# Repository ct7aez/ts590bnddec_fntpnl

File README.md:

# ts590bnddec_fntpnl
LCD display and buttons for the TS-590 band Decoder.
This is the pcb and sch design for the front panel of the TS-590S(G) Arduino based Band Decoder.
Made by João Cunha Lopes, CT2HME and Pedro Correia, CT7AEZ.
This pcb allows direct connection with the TS-590S(G) Arduino based Band Decoder and provides easy access to the menu buttons and LCD.

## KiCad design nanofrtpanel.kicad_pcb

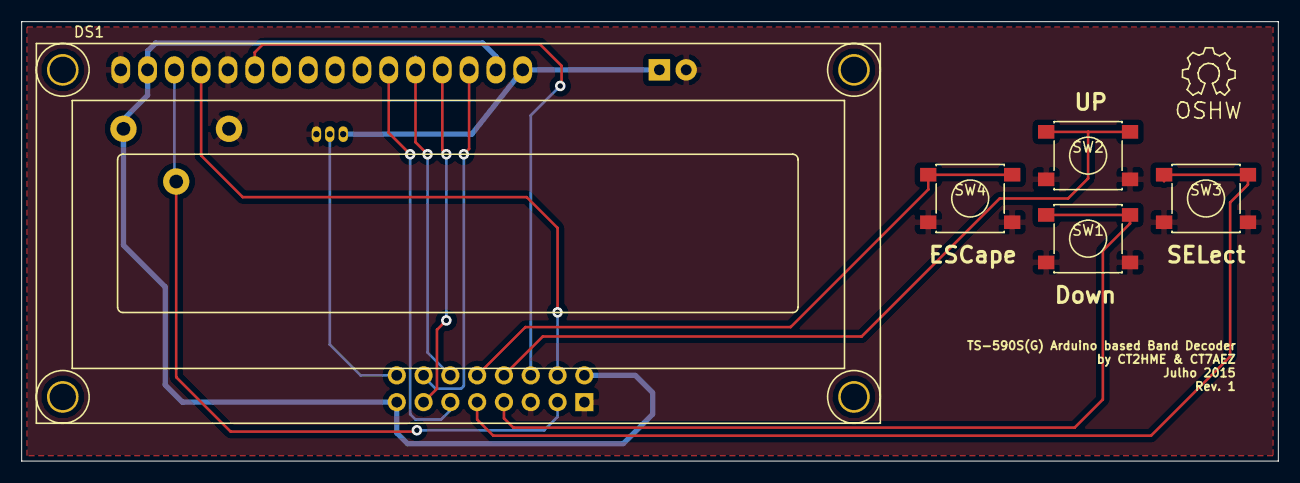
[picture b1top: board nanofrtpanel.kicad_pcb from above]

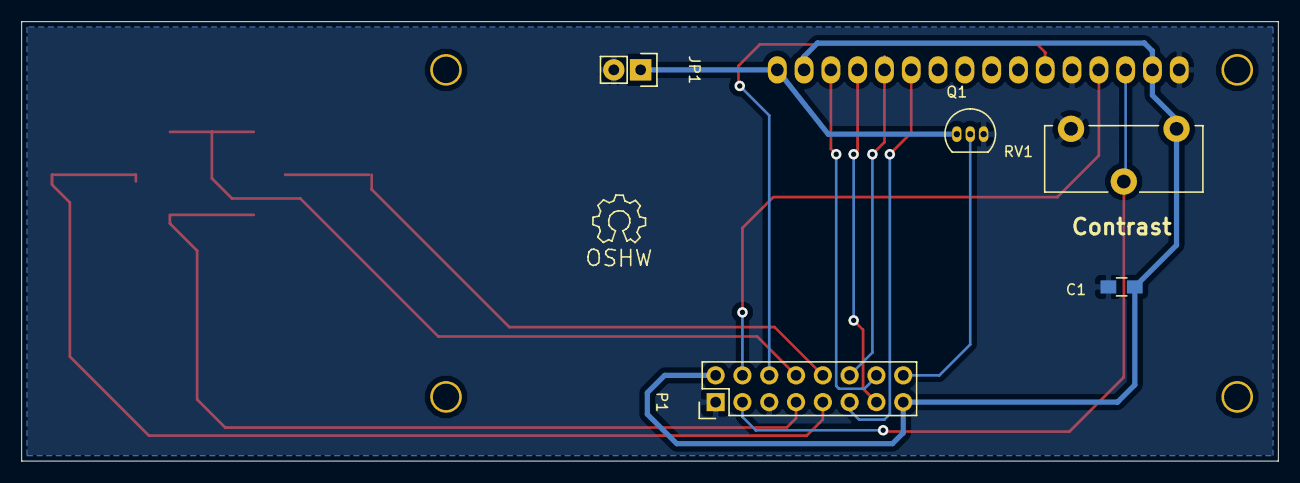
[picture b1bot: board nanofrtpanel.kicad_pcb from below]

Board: 2 copper layers, 119.1 x 41.7 mm, 10 parts (5 on the bottom side), 15 nets.

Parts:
C1: 100n; C_0805_HandSoldering
DS1: LCD-016N002L; WC1602A
JP1: Jumper_NO_Small; Pin_Header_Straight_1x02
P1: CONN_02X08; Pin_Header_Straight_2x08
Q1: BS170; TO-92_Inline_Narrow_Oval
RV1: 10K; Potentiometer_Trimmer-Piher-PT15-h5_vertical
SW1: DOWN; SW_SPST_PTS645
SW2: UP; SW_SPST_PTS645
SW3: SELECT; SW_SPST_PTS645
SW4: ESC; SW_SPST_PTS645

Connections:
+5V: C1.1, DS1.2, DS1.15, P1.2, P1.15, RV1.1
/BCKL: P1.16, Q1.2
/D2: DS1.14, P1.14
/D3: DS1.13, P1.13
/D4: DS1.12, P1.12
/D5: DS1.11, P1.11
/D11: DS1.6, P1.6
/D12: DS1.4, P1.4
/SW1: P1.7, SW1.1
/SW2: P1.8, SW2.1
/SW3: P1.9, SW3.1
/SW4: P1.10, SW4.1
/VO: DS1.3, P1.3, RV1.2
GND: C1.2, DS1.1, DS1.5, JP1.2, P1.1, P1.5, Q1.3, RV1.3, SW1.2, SW2.2, SW3.2, SW4.2
unnamed: DS1.16, JP1.1, Q1.1

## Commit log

2015-07-19 kick off
2015-07-21 Better access to RV1 and rebuild to be compatible.
2015-07-21 Full comp with band decoder and better access to RV1
2015-07-21 silkscreen update
